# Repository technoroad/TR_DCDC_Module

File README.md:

# TR_DCDC_Module
TR製DCDCモジュール（ストロベリーリナックス製LT3790モジュールの代替品）

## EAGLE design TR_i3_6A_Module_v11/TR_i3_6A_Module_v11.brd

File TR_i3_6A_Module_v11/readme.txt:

---------------------------------------------------------------

RS-274X File List

---------------------------------------------------------------
* Outline		TR_i3_6A_Module_v11.out
* Top Side		TR_i3_6A_Module_v11.cmp
* Bottom Side		TR_i3_6A_Module_v11.sol

* Top Silkscreen	TR_i3_6A_Module_v11.plc
* Bottom Silkscreen	TR_i3_6A_Module_v11.pls

* Top Soldermask	TR_i3_6A_Module_v11.stc
* Bottom Soldermask	TR_i3_6A_Module_v11.sts

* Top Metal Mask	TR_i3_6A_Module_v11.mmc
* Bottom Metal Mask	TR_i3_6A_Module_v11.mms

* Drill List		TR_i3_6A_Module_v11.drl
* Drill Data1		TR_i3_6A_Module_v11.drd
* Drill Data2		TR_i3_6A_Module_v11.dri

---------------------------------------------------------------

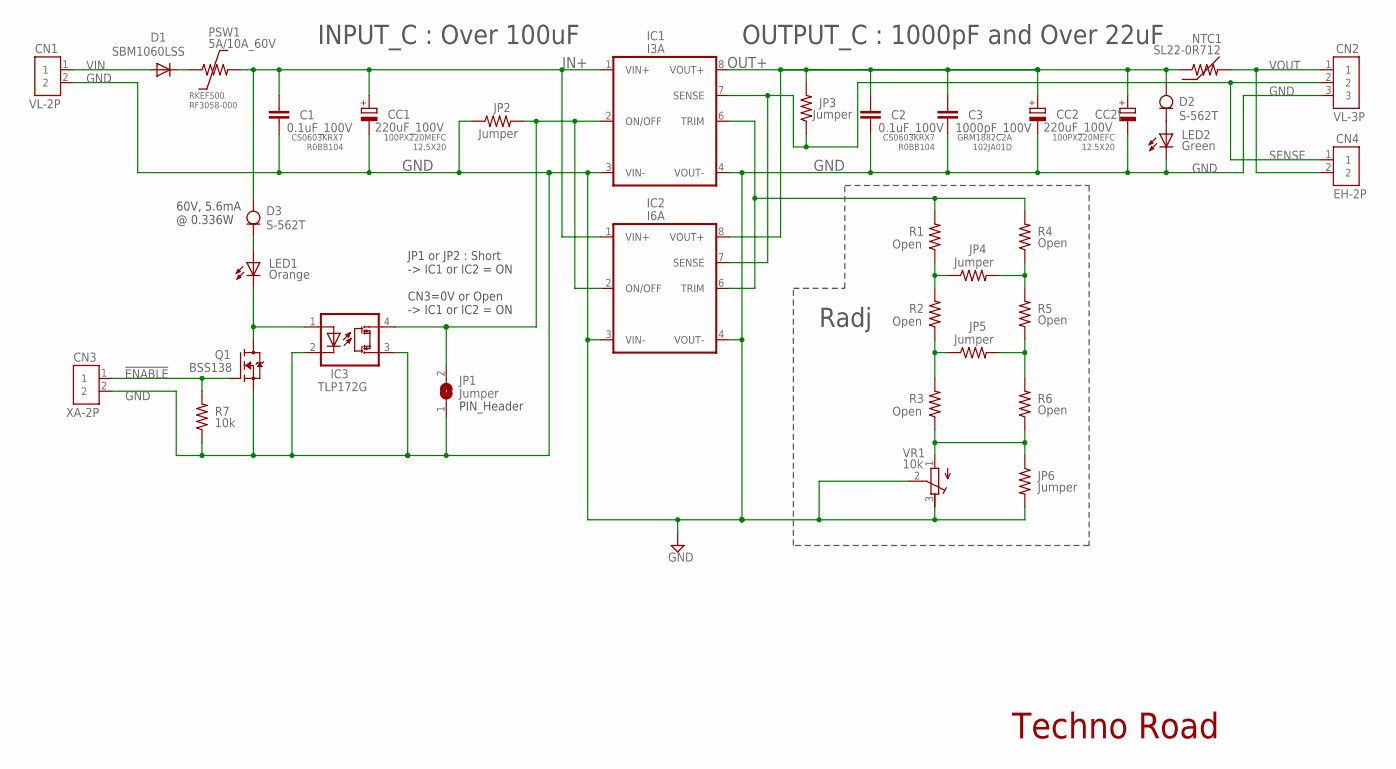
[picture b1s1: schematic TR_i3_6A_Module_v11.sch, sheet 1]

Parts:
C1, C2: 0.1uF_100V; C1608
C3: 1000pF_100V; C1608
CC1, CC2: 220uF_100V; CC0510
CC2\: CPOL-EUE7.5-16; E7,5-16
CN1: VL-2P; VL3-2P
CN2: VL-3P; VL3-3P
CN3: XA-2P; XA-2P_NH
CN4: EH-2P
D1: SBM1060LSS; 12.7MM
D2, D3: S-562T; S-XXXT
IC1: I3A; I3A_SERIES
IC2: I6A; I6A_SERIES
IC3: TLP172G; 11-5H1
JP1: Jumper; JP1D_HOLE
JP2, JP3, JP4, JP5, JP6: Jumper; R1608_LARGE_PAD
LED1: Orange; SML1608
LED2: Green; SML1608
NTC1: SL22-0R712; SL22
PSW1: 5A/10A_60V; PSW-10.16MM_4MM
Q1: BSS138; SOT-23-3
R1, R2, R3, R4, R5, R6: Open; R1608_LARGE_PAD
R7: 10k; R1608_LARGE_PAD
VR1: 10k; 3361P

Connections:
!ENABLE: CN3.1, Q1.1 (G), R7.2
D_PSW: D1.2 (C), PSW1.1
GND: C1.2, C2.2, C3.2, CC1.-, CC2.-, CC2\.-, CN1.2, CN2.3, CN3.2, IC1.3 (VIN-), IC1.4 (VOUT-), IC2.3 (VIN-), IC2.4 (VOUT-), IC3.2 (C1), IC3.3 (DRN1), JP1.1, JP2.1, JP6.2, LED2.C, Q1.2 (S), R7.1, VR1.2 (S), VR1.3 (E)
IN+: C1.1, CC1.+, D3.A, IC1.1 (VIN+), IC2.1 (VIN+), PSW1.2
unnamed: JP6.1, R3.1, R6.1, VR1.1 (A)
unnamed: JP4.1, R1.1, R2.2
unnamed: JP5.1, R2.1, R3.2
unnamed: IC1.2 (ON/OFF), IC2.2 (ON/OFF), IC3.4 (DRN2), JP1.2, JP2.2
unnamed: D2.C, LED2.A
unnamed: D3.C, LED1.A
unnamed: IC1.6 (TRIM), IC2.6 (TRIM), R1.2, R4.2
unnamed: JP4.2, R4.1, R5.2
unnamed: JP5.2, R5.1, R6.2
unnamed: IC3.1 (A1), LED1.C, Q1.3 (D)
OUT+: C2.1, C3.1, CC2.+, CC2\.+, D2.A, IC1.8 (VOUT+), IC2.8 (VOUT+), JP3.2, NTC1.1
SENSE: CN2.2, CN4.1, IC1.7 (SENSE), IC2.7 (SENSE), JP3.1
VIN: CN1.1, D1.1 (A)
VOUT: CN2.1, CN4.2, NTC1.2

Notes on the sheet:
OUTPUT_C : 1000pF and Over 22uF
INPUT_C : Over 100uF
Techno Road
Radj
JP1 or JP2 : Short -> IC1 or IC2 = ON CN3=0V or Open -> IC1 or IC2 = ON
100PX220MEFC 12.5X20
CS0603KRX7 R0BB104
GRM1882C2A 102JA01D
PIN_Header
60V, 5.6mA @ 0.336W
RKEF500 RF3058-000

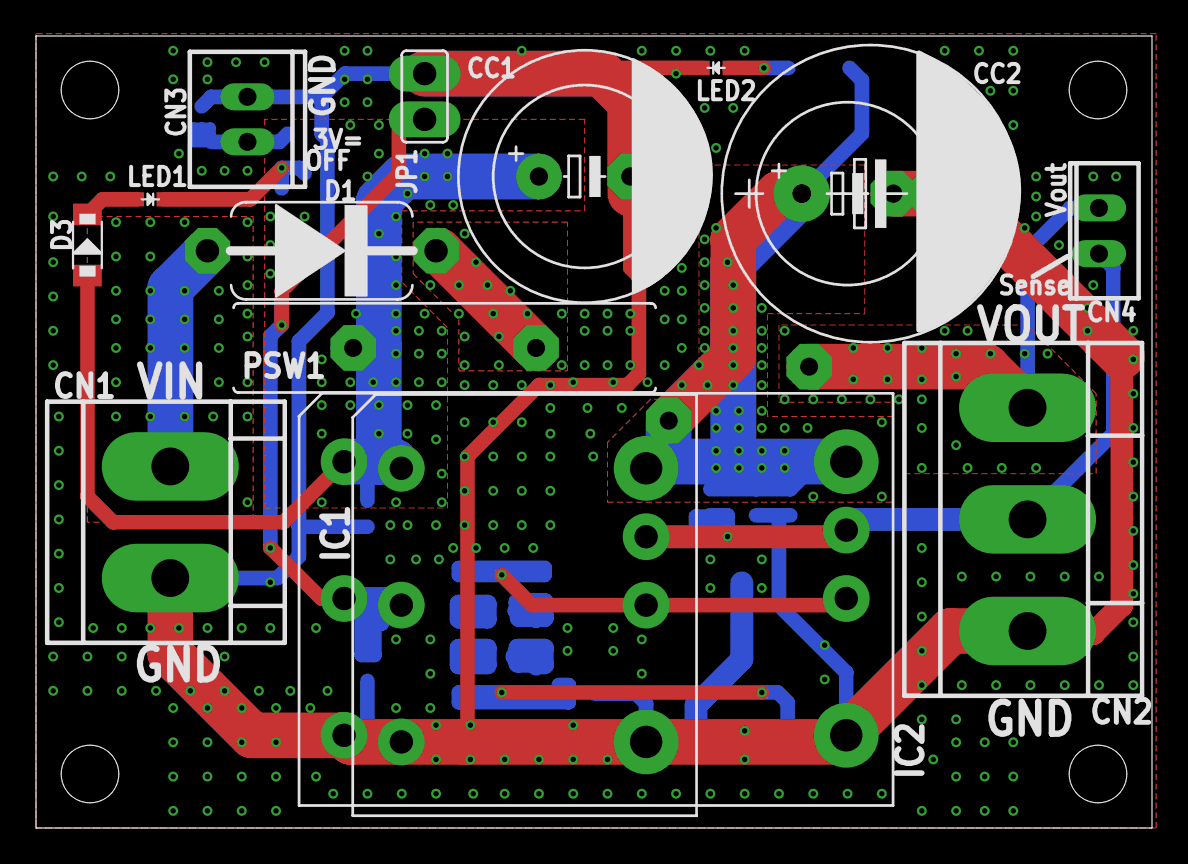
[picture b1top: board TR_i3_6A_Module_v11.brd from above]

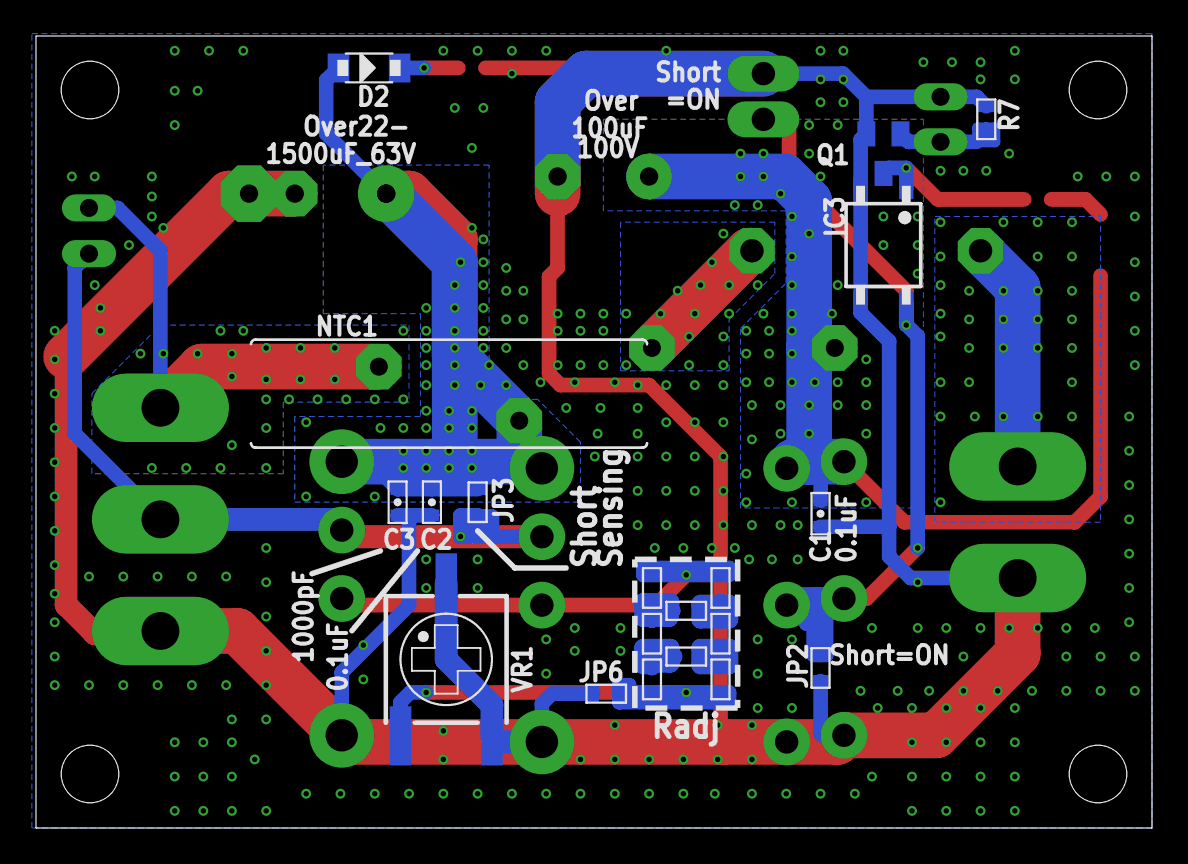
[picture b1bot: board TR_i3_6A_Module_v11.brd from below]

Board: 2 copper layers, 62.0 x 44.0 mm, 35 parts (20 on the bottom side), 18 nets.

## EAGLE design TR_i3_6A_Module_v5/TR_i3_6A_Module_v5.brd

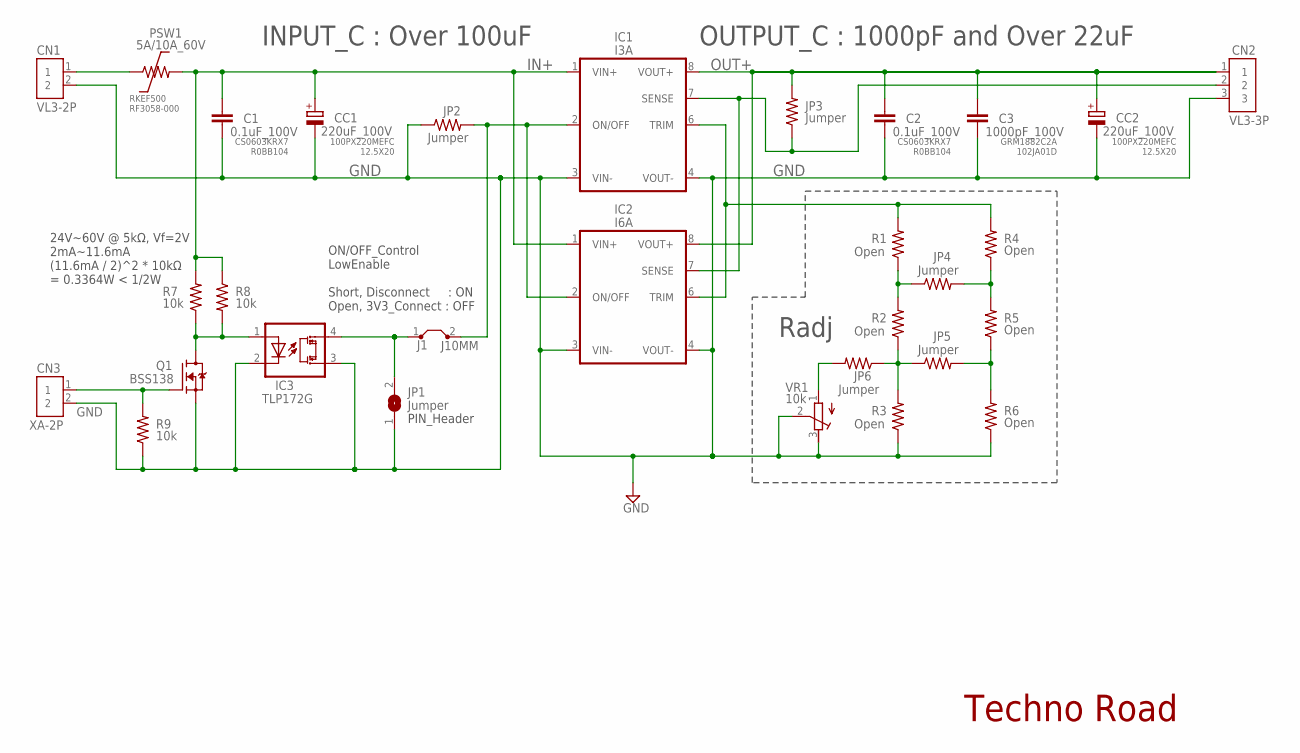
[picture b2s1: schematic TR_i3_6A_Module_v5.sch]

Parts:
C1, C2: 0.1uF_100V; C1608
C3: 1000pF_100V; C1608
CC1, CC2: 220uF_100V; CC0510
CN1: VL3-2P
CN2: VL3-3P
CN3: XA-2P; XA-2P_NH
IC1: I3A; I3A_SERIES
IC2: I6A; I6A_SERIES
IC3: TLP172G; 11-5H1
J1: J10MM; 10
JP1: Jumper; JP1D_HOLE
JP2, JP3, JP4, JP5, JP6: Jumper; R1608_LARGE_PAD
PSW1: 5A/10A_60V; PSW-10.16MM_4MM
Q1: BSS138; SOT-23-3
R1, R2, R3, R4, R5, R6: Open; R1608_LARGE_PAD
R7, R8: 10k; 0204V
R9: 10k; R1608_LARGE_PAD
VR1: 10k; 3361P

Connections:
GND: C1.2, C2.2, C3.2, CC1.-, CC2.-, CN1.2, CN2.3, CN3.2, IC1.3 (VIN-), IC1.4 (VOUT-), IC2.3 (VIN-), IC2.4 (VOUT-), IC3.2 (C1), IC3.3 (DRN1), JP1.1, JP2.1, Q1.2 (S), R3.1, R6.1, R9.1, VR1.2 (S), VR1.3 (E)
IN+: C1.1, CC1.+, IC1.1 (VIN+), IC2.1 (VIN+), PSW1.2, R7.2, R8.1
unnamed: JP4.1, R1.1, R2.2
unnamed: JP5.1, JP6.1, R2.1, R3.2
unnamed: IC3.4 (DRN2), J1.1, JP1.2
unnamed: CN2.2, IC1.7 (SENSE), IC2.7 (SENSE), JP3.1
unnamed: IC1.2 (ON/OFF), IC2.2 (ON/OFF), J1.2, JP2.2
unnamed: IC1.6 (TRIM), IC2.6 (TRIM), R1.2, R4.2
unnamed: JP4.2, R4.1, R5.2
unnamed: JP5.2, R5.1, R6.2
unnamed: IC3.1 (A1), Q1.3 (D), R7.1, R8.2
unnamed: CN1.1, PSW1.1
unnamed: JP6.2, VR1.1 (A)
unnamed: CN3.1, Q1.1 (G), R9.2
OUT+: C2.1, C3.1, CC2.+, CN2.1, IC1.8 (VOUT+), IC2.8 (VOUT+), JP3.2

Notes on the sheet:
OUTPUT_C : 1000pF and Over 22uF
INPUT_C : Over 100uF
Techno Road
Radj
ON/OFF_Control LowEnable Short, Disconnect : ON Open, 3V3_Connect : OFF
100PX220MEFC 12.5X20
CS0603KRX7 R0BB104
GRM1882C2A 102JA01D
PIN_Header
24V~60V @ 5kΩ, Vf=2V 2mA~11.6mA (11.6mA / 2)^2 * 10kΩ = 0.3364W < 1/2W
RKEF500 RF3058-000

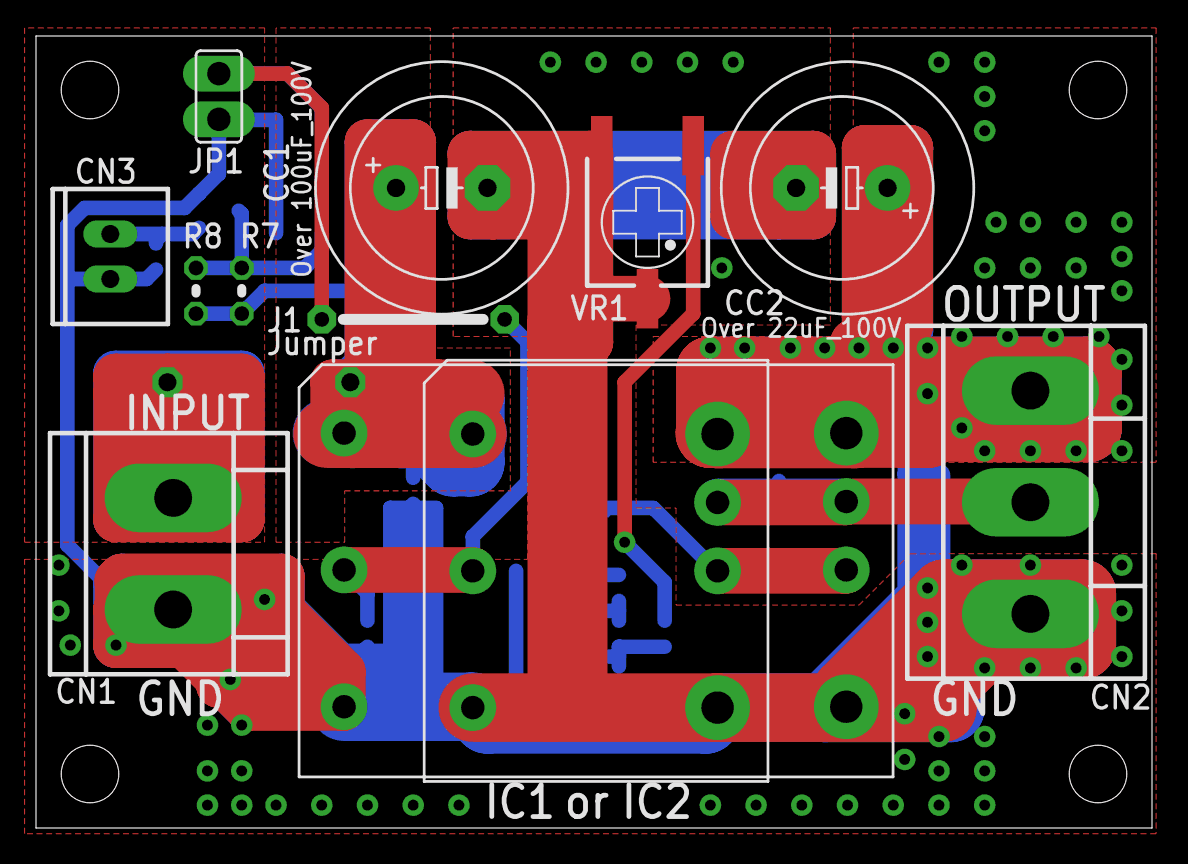
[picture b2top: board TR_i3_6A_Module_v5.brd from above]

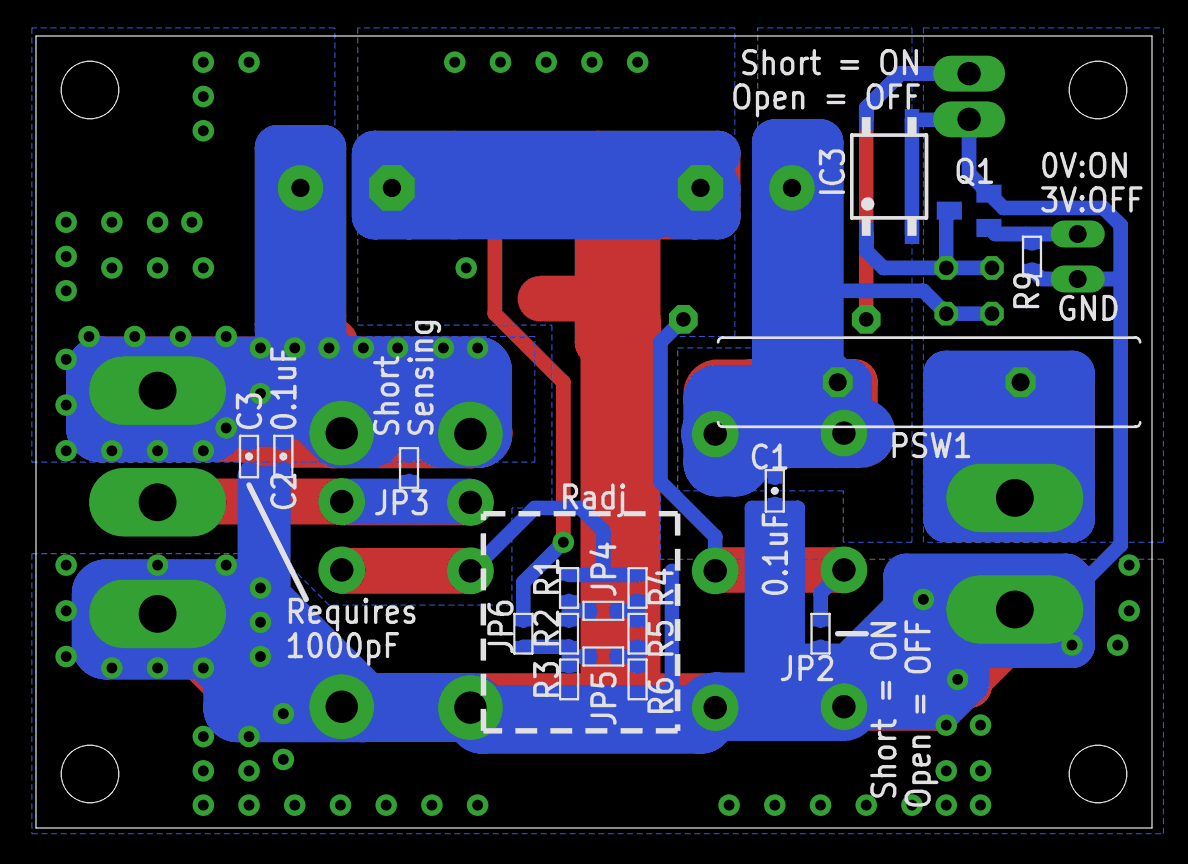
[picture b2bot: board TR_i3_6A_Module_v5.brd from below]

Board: 2 copper layers, 62.0 x 44.0 mm, 30 parts (18 on the bottom side), 15 nets.

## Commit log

2022-10-03 ストロベリーリナックスのLT3970モジュールの代替品
    5Gロボット以前（5Gロボット含む）で使用
2022-10-03 no message
2022-10-03 Revert "ストロベリーリナックスのLT3790モジュールの代替品"
    This reverts commit fc3d5e599f8793499d1b9bfd4d8ecacdd8420709.
2022-10-03 TR製DCDCモジュール（ストロベリーリナックスのLT3790モジュールの代替品）
    5Gロボット以前（5Gロボット含む）に使用のTR製DCDCモジュール
2022-10-04 TR製DCDCモジュール（ストロベリーリナックスのLT3790モジュールの代替品）
    5Gロボットより後に使用予定の“新”TR製DCDCモジュール
2022-12-15 TR製DCDCモジュール（ストロベリーリナックスのLT3790モジュールの代替品）
    v10の基板のコネクタを元に戻し、はんだ盛り部分を無くしたもの。
2022-12-16 TR製DCDCモジュール（ストロベリーリナックスのLT3790モジュールの代替品）
    レイアウト修正
2022-12-19 TR製DCDCモジュール（ストロベリーリナックスのLT3790モジュールの代替品）
    レイアウト・ビア修正
2022-12-20 TR製DCDCモジュール（ストロベリーリナックスのLT3790モジュールの代替品）
    部品表、計算表追加
2022-12-20 TR製DCDCモジュール（ストロベリーリナックスのLT3790モジュールの代替品）
    基板データ更新
2022-12-20 TR製DCDCモジュール（ストロベリーリナックスのLT3790モジュールの代替品）
    レジスト開口部の修正。（指摘画像あり）
